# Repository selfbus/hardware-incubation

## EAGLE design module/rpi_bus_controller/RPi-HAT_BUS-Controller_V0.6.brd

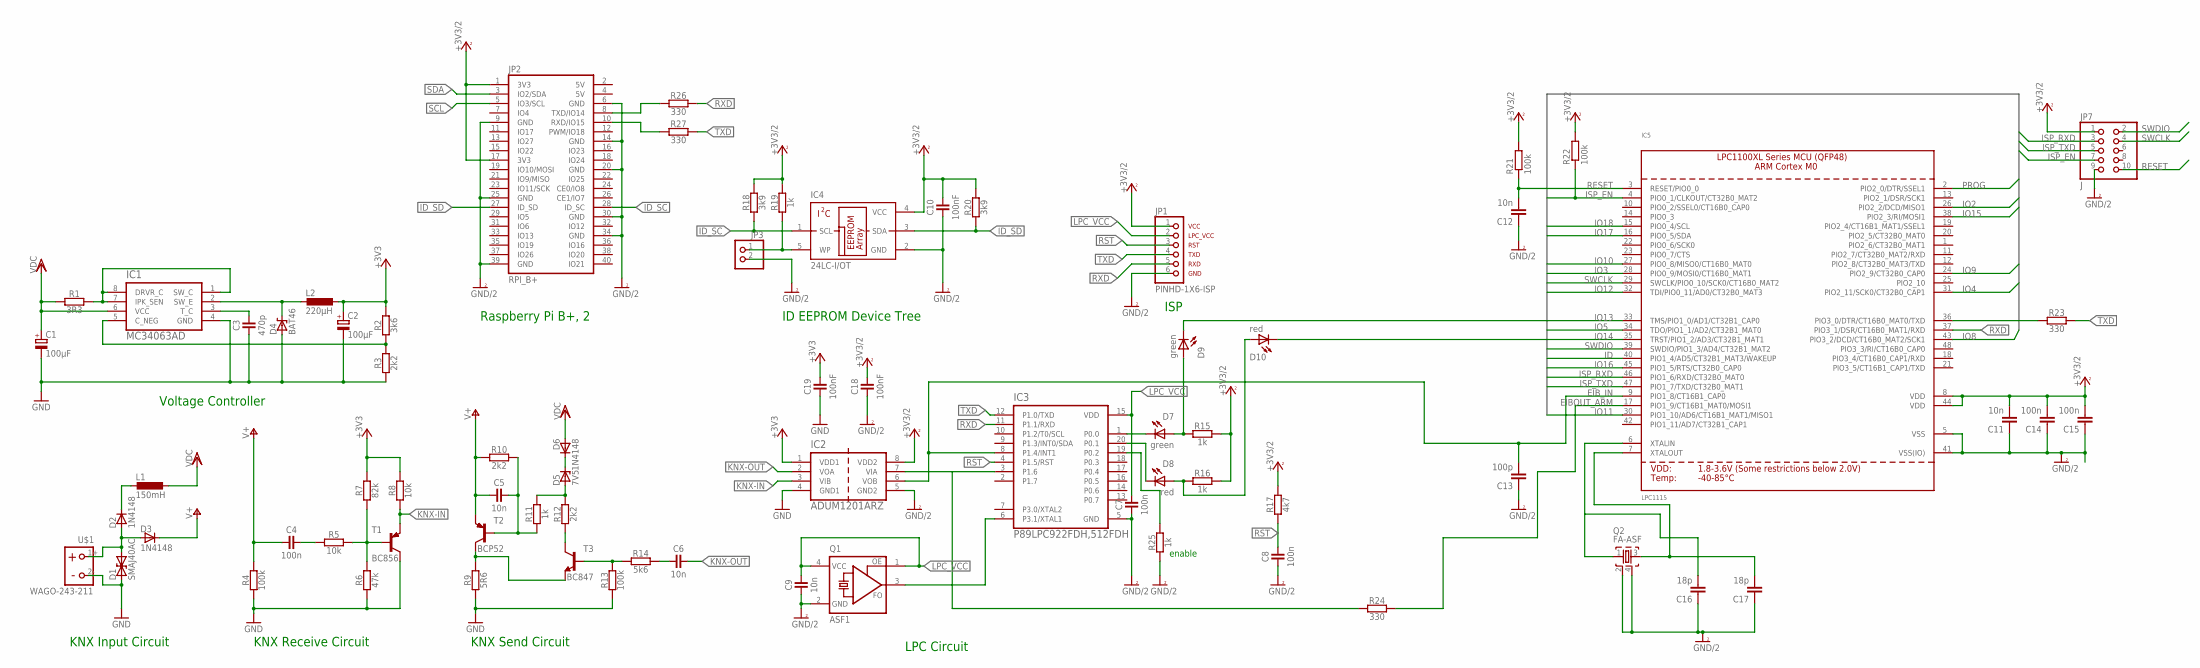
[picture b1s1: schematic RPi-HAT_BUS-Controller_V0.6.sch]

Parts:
C1: 100µF; PANASONIC_D
C2: 100µF; PANASONIC_C
C3: 470p; R1206
C4, C7, C8: 100n; R1206
C5, C6, C9: 10n; R1206
C10, C18, C19: 100nF; R1206
C11, C12: 10n; C1206
C13: 100p; C1206
C14, C15: 100n; C1206
C16, C17: 18p; C1206
D1: SMAJ40AC; DO-214AC
D2, D3, D6: 1N4148; MINIMELF
D4: BAT46; MINIMELF
D5: 7V5; MINIMELF
D7, D9: green; CHIPLED_1206
D8, D10: red; CHIPLED_1206
IC1: MC34063AD; SOIC127P600X175-8N
IC2: ADUM1201ARZ; SOIC127P600X175-8N
IC3: P89LPC922FDH,512FDH; SOP65P640X110-20N
IC4: 24LC-I/OT; SOT23-5
IC5: LPC1115; LQFP48
JP1: PINHD-1X6-ISP; 1X06
JP2: RPI_B+; RPI-B+HAT
JP3: PINHD-1X2; 1X02
JP7: J; 2X05M
L1: 150mH; 11P-L1
L2: 220µH; 2200-11.43
Q1: ASF1; ASF
Q2: FA-ASF; ASF
R1: 3R3; R1206
R2: 3k6; R1206
R3, R10, R12: 2k2; R1206
R4, R13, R21, R22: 100k; R1206
R5, R8: 10k; R1206
R6: 47k; R1206
R7: 82k; R1206
R9: 5R6; R1206
R11, R15, R16, R19, R25: 1k; R1206
R14: 5k6; R1206
R17: 4k7; R1206
R18, R20: 3k9; R1206
R23, R24, R26, R27: 330; R1206
T1: BC856; SOT23
T2: BCP52; SOT223
T3: BC847; SOT23
U$1: WAGO-243-211

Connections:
+3V3: C2.+, C19.2, IC2.1 (VDD1), L2.1, R2.2, R7.2, R8.2
+3V3/2: C10.2, C11.2, C14.2, C15.2, C18.2, IC2.8 (VDD2), IC4.4 (VCC), IC5.8 (VDD), IC5.44 (VDD), JP1.1, JP2.1 (3V3), JP2.17 (3V3), JP7.1, R15.2, R16.2, R17.2, R18.2, R19.2, R20.2, R21.2, R22.2
EIBOUT_ARM: IC5.17 (PIO1_9/CT16B1_MAT0/MOSI1), R24.2
EIB_IN: C13.2, IC2.6 (VOB), IC3.8 (P1.4/INT1), IC5.9 (PIO1_8/CT16B1_CAP0)
EIB_OUT: IC2.7 (VIA), IC3.3 (P1.6), R24.1
GND: C1.-, C2.-, C3.1, C19.1, D1.A, D4.A, IC1.4 (GND), IC2.4 (GND1), R3.1, R4.1, R6.1, R9.1, R13.1, T1.3 (C), U$1.2-
GND/2: C7.1, C8.1, C9.1, C10.1, C11.1, C12.1, C13.1, C14.1, C15.1, C16.1, C17.1, C18.1, IC2.5 (GND2), IC3.5 (GND), IC4.2 (GND), IC5.5 (VSS), IC5.41 (VSS(IO)), JP1.6, JP2.6 (GND), JP2.9 (GND), JP2.14 (GND), JP2.20 (GND), JP2.25 (GND), JP2.30 (GND), JP2.34 (GND), JP2.39 (GND), JP3.2, JP7.9, Q1.2 (GND), Q2.2, Q2.4, R25.1
ID: IC5.40 (PIO1_4/AD5/CT32B1_MAT3/WAKEUP)
ID_SC: IC4.1 (SCL), JP2.28 (ID_SC), R18.1
ID_SD: IC4.3 (SDA), JP2.27 (ID_SD), R20.1
IO2: IC5.26 (PIO2_2/DCD/MISO1)
IO3: IC5.28 (PIO0_9/MOSI0/CT16B0_MAT1)
IO4: IC5.31 (PIO2_11/SCK0/CT32B0_CAP1)
IO5: IC5.34 (TDO/PIO1_1/AD2/CT32B1_MAT0)
IO8: IC5.43 (PIO3_2/DCD/CT16B0_MAT2/SCK1)
IO9: IC5.24 (PIO2_9/CT32B0_CAP0)
IO10: IC5.27 (PIO0_8/MISO0/CT16B0_MAT0)
IO11: IC5.30 (PIO1_10/AD6/CT16B1_MAT1/MISO1)
IO12: D10.C, IC5.32 (TDI/PIO0_11/AD0/CT32B0_MAT3)
IO13: IC5.33 (TMS/PIO1_0/AD1/CT32B1_CAP0)
IO14: IC5.35 (TRST/PIO1_2/AD3/CT32B1_MAT1)
IO15: D9.C, IC5.38 (PIO2_3/RI/MOSI1)
IO16: IC5.45 (PIO1_5/RTS/CT32B0_CAP0)
IO17: IC5.16 (PIO0_5/SDA)
IO18: IC5.15 (PIO0_4/SCL)
ISP_EN: IC5.4 (PIO0_1/CLKOUT/CT32B0_MAT2), JP7.7, R22.1
ISP_RXD: IC5.46 (PIO1_6/RXD/CT32B0_MAT0), JP7.3
ISP_TXD: IC5.47 (PIO1_7/TXD/CT32B0_MAT1), JP7.5
KNX-IN: IC2.3 (VIB), R8.1, T1.2 (E)
KNX-OUT: C6.2, IC2.2 (VOA)
LPC_VCC: C7.2, C9.2, IC3.15 (VDD), JP1.2, Q1.1 (OE), Q1.4 (VCC)
unnamed: D1.C, D2.A, D3.A, U$1.1+
unnamed: C16.2, IC5.6 (XTALIN), Q2.1
unnamed: IC1.5 (C_NEG), R2.1, R3.2
unnamed: C4.2, R5.1
unnamed: D2.C, L1.2
unnamed: R5.2, R6.2, R7.1, T1.1 (B)
unnamed: C17.2, IC5.7 (XTALOUT), Q2.3
unnamed: IC1.1 (SW_C), IC1.7 (IPK_SEN), IC1.8 (DRVR_C), R1.2
unnamed: D8.C, IC3.20 (P0.1)
unnamed: C3.2, IC1.3 (T_C)
unnamed: D7.C, IC3.1 (P0.0)
unnamed: IC4.5 (WP), JP3.1, R19.1
unnamed: D4.C, IC1.2 (SW_E), L2.2
unnamed: IC3.19 (P0.2), R25.2
unnamed: JP2.8 (TXD/IO14), R26.1
unnamed: JP2.10 (RXD/IO15), R27.1
unnamed: R9.2, T2.2 (C), T2.4 (C), T3.2 (E)
unnamed: C5.2, R10.2, R11.1, T2.1 (B)
unnamed: D5.A, R11.2, R12.2
unnamed: R12.1, T3.3 (C)
unnamed: R13.2, R14.1, T3.1 (B)
unnamed: C6.1, R14.2
unnamed: D5.C, D6.C
unnamed: IC3.6 (P3.1/XTAL1), Q1.3 (FO)
unnamed: D7.A, D9.A, R15.1
unnamed: D8.A, D10.A, R16.1
PROG: IC5.2 (PIO2_0/DTR/SSEL1)
RESET: C12.2, IC5.3 (RESET/PIO0_0), JP7.10, R21.1
RST: C8.2, IC3.4 (P1.5/RST), JP1.3, R17.1
RXD: IC3.11 (P1.1/RXD), IC5.37 (PIO3_1/DSR/CT16B0_MAT1/RXD), JP1.5, R26.2
SCL: JP2.5 (IO3/SCL)
SDA: JP2.3 (IO2/SDA)
SWCLK: IC5.29 (SWCLK/PIO0_10/SCK0/CT16B0_MAT2), JP7.4
SWDIO: IC5.39 (SWDIO/PIO1_3/AD4/CT32B1_MAT2), JP7.2
TXD: IC3.12 (P1.0/TXD), JP1.4, R23.2, R27.2
TXD_ARM: IC5.36 (PIO3_0/DTR/CT16B0_MAT0/TXD), R23.1
V+: C4.1, C5.1, D3.C, R4.2, R10.1, T2.3 (E)
VDD: C1.+, D6.A, IC1.6 (VCC), L1.1, R1.1

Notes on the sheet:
KNX Input Circuit
Voltage Controller
KNX Receive Circuit
KNX Send Circuit
Raspberry Pi B+, 2
ISP
LPC Circuit
ID EEPROM Device Tree
enable

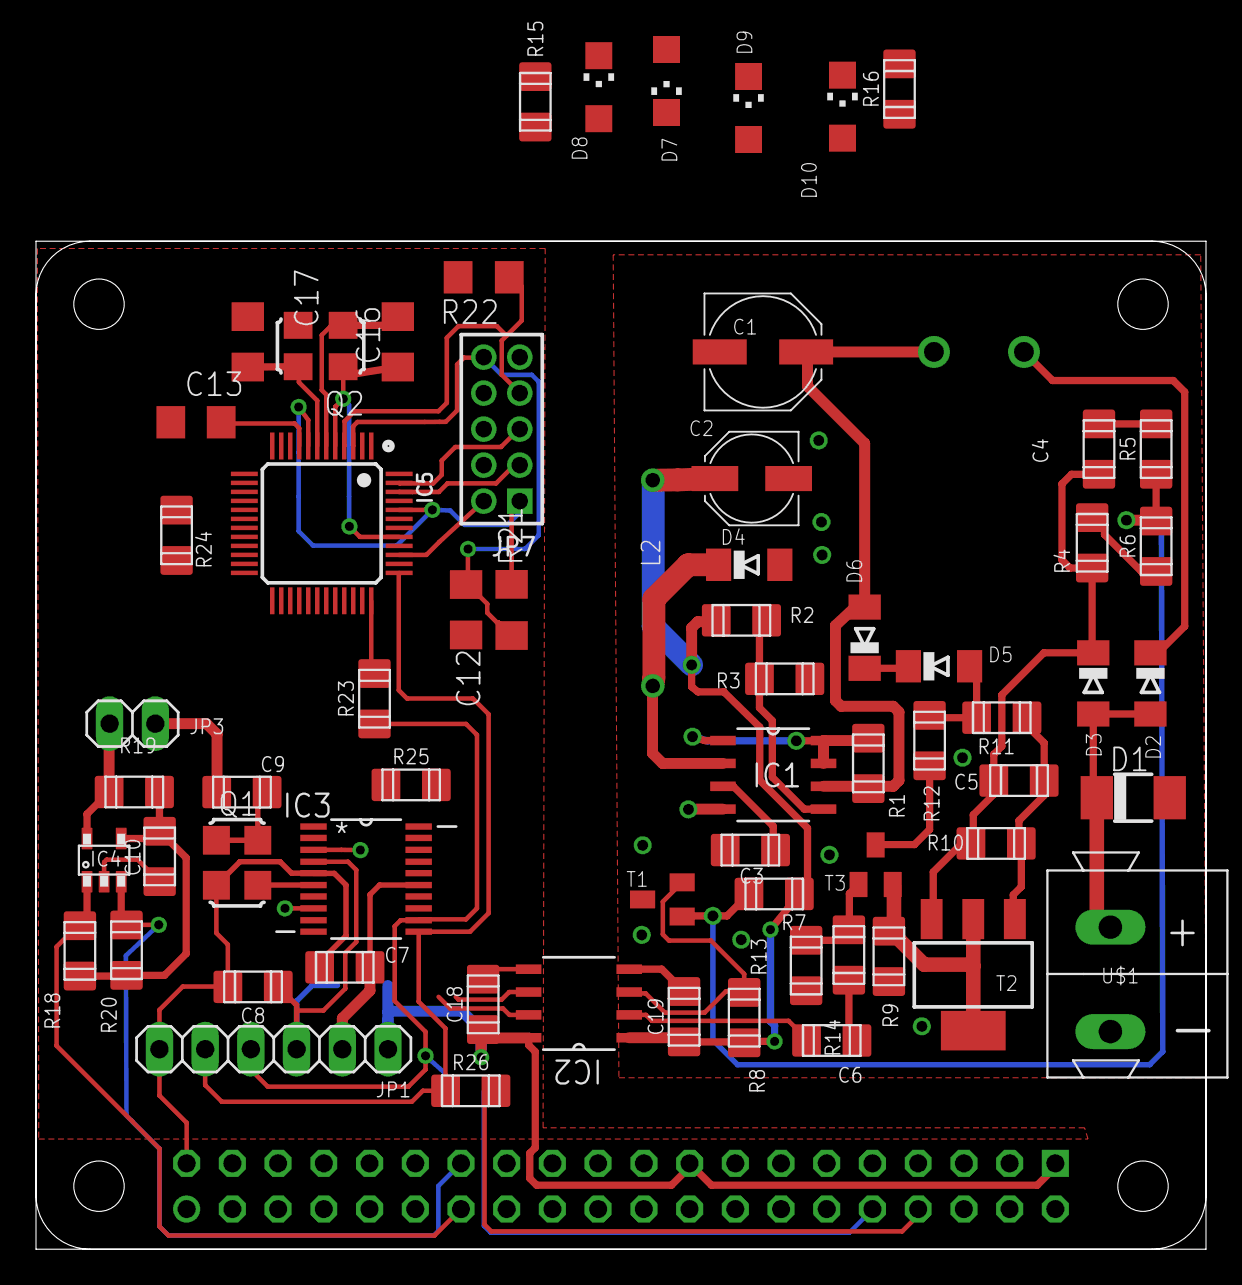
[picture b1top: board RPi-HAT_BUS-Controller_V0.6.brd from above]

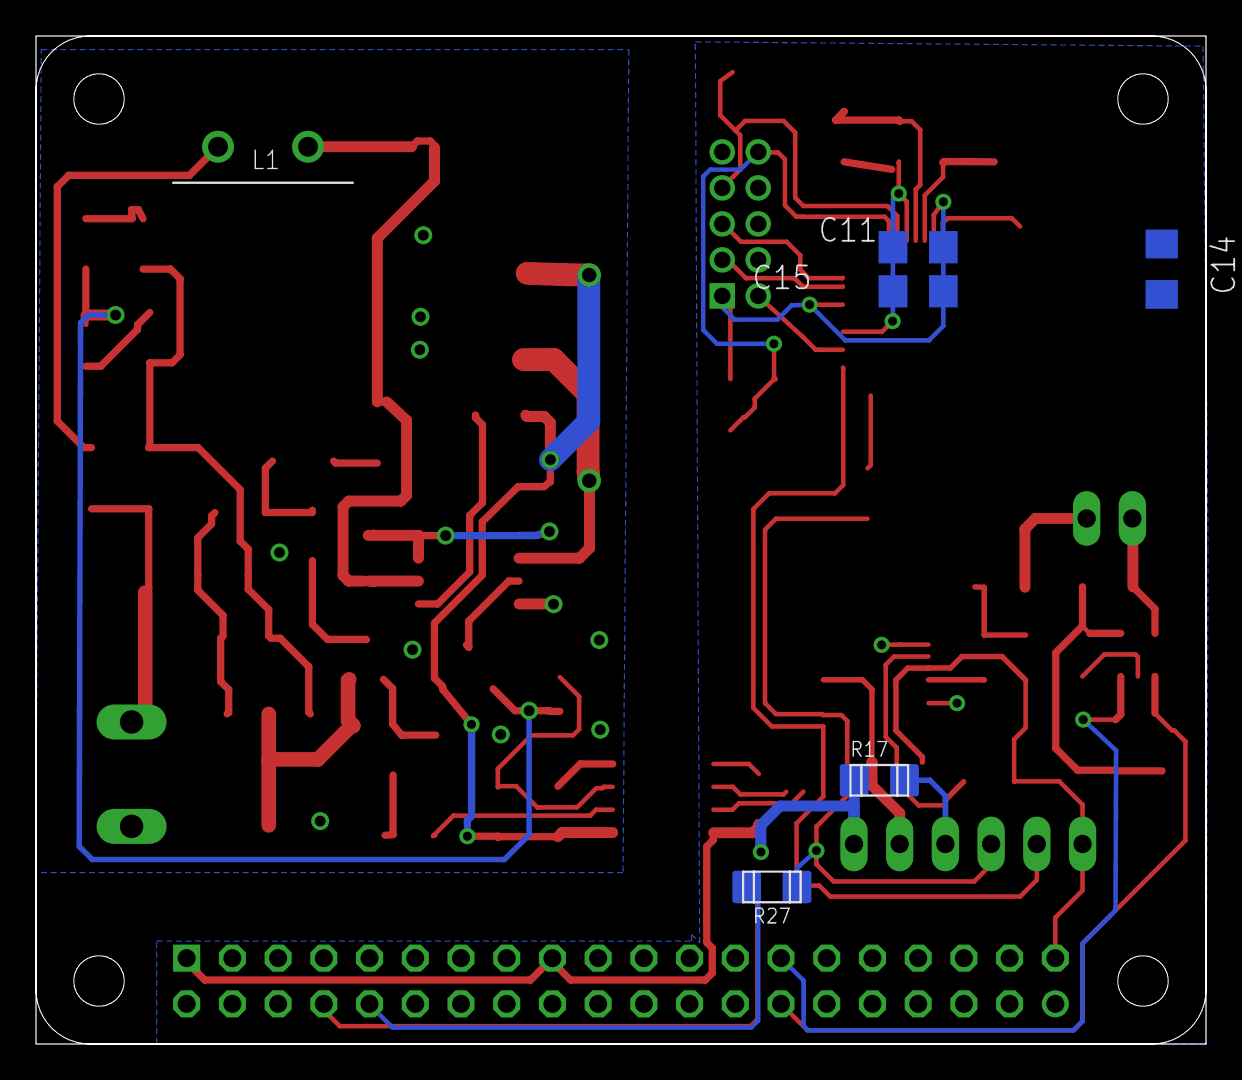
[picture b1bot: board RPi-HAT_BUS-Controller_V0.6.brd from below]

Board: 2 copper layers, 65.0 x 56.0 mm, 73 parts (6 on the bottom side), 52 nets.

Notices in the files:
parts and their libraries:
microbuilder: This work is placed in the public domain, and may be freely used for commercial and non-commercial work with the following conditions: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
